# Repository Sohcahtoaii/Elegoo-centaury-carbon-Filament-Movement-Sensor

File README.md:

# Elegoo Centaury Carbon – Filament Movement Sensor  
### FR / EN – Capteur de mouvement de filament pour imprimante 3D

---

## 🇫🇷 Description (FR)

🔧 Ce projet est une **amélioration matérielle** pour l’imprimante **Elegoo Centaury Carbon**, permettant de détecter le mouvement du filament.  
Il est basé sur le travail de [Jonathan Rowny](https://github.com/jrowny/cc_sfs), avec comme principale contribution ici la **création d’un PCB personnalisé** pour faciliter l’intégration propre du capteur.

📦 **Capteur requis :**  
👉 Ce projet utilise le **BIGTREETECH Smart Filament Detector V2.0**, un capteur optique à encodeur rotatif.

🔌 **PCB personnalisé :**  
- Fichiers créés avec **KiCad**
- Connexion facile au capteur et à la Centaury
- Ports supplémentaires disponibles pour le **debug ou des améliorations futures**

📁 Tous les fichiers nécessaires sont disponibles dans le dossier `/pcb` :
- `.kicad_pcb`, `.sch`, fichiers Gerber, PDF
- Sérigraphie, dimensions, BOM (Bill of Materials)

---

## 🇬🇧 Description (EN)

🔧 This project is a **hardware upgrade** for the **Elegoo Centaury Carbon** 3D printer that adds **filament motion detection**.  
It is based on the work by [Jonathan Rowny](https://github.com/jrowny/cc_sfs), with the main contribution here being a **custom-designed PCB** to neatly integrate the sensor.

📦 **Required sensor:**  
👉 This project uses the **BIGTREETECH Smart Filament Detector V2.0**, an optical rotary encoder sensor.

🔌 **Custom PCB:**
- Designed with **KiCad**
- Easy connection to the sensor and the Centaury printer
- Additional ports are available for **debugging or future upgrades**

📁 All necessary files are in the `/pcb` folder:
- `.kicad_pcb`, `.sch`, Gerber files, PDFs
- Silkscreen, dimensions, BOM (Bill of Materials)

---

## 🔗 Projet original / Original Project

📚 Basé sur / Based on:  
👉 [Jonathan Rowny – cc_sfs](https://github.com/jrowny/cc_sfs)

---

## 🧰 Matériel requis / Required Hardware

- BIGTREETECH Smart Filament Detector V2.0  
- Résistances, connecteurs, composants SMD ou traversants  
- Câbles dupont ou connecteurs JST selon le montage  
- PCB personnalisé  
- Outils de soudure  
- Imprimante 3D : **Elegoo Centaury Carbon**

---

## ⚙️ Instructions de montage / Assembly Instructions

### 🇫🇷 En français

1. Soudez les composants sur le PCB selon le schéma si vous n'avez pas utilisé un service d’assemblage.  
2. Connectez le capteur BTT V2.0 au PCB.  
3. Branchez le PCB à l'imprimante selon le câblage prévu.  
4. Flashez le firmware proposé dans le projet de [Jonathan Rowny](https://github.com/jrowny/cc_sfs).  
5. Vérifiez la détection du filament via le firmware (compatible Marlin ou Klipper).  
6. Utilisez les **ports restants** pour du debug ou des extensions.

### 🇬🇧 In English

1. Solder the components onto the PCB, unless you're using an assembled PCB service.  
2. Connect the BTT Smart Filament Sensor V2.0 to the PCB.  
3. Connect the PCB to your Elegoo printer using the proper wiring.  
4. Flash the firmware provided in [Jonathan Rowny’s project](https://github.com/jrowny/cc_sfs).  
5. Verify filament movement detection through the firmware (Marlin or Klipper compatible).  
6. Use the **extra ports** for debugging or optional upgrades.

---
## 🔍 BOM interactif  
👉 [Voir le BOM interactif ici](https://sohcahtoaii.github.io/Elegoo-centaury-carbon-Filament-Movement-Sensor/)

## 🖼️ Images / Preview

---

## ❓ FAQ

**Q : Le capteur fonctionne-t-il avec d'autres imprimantes ?**  
A : Ce design est principalement prévu pour l’Elegoo Centaury Carbon, mais le PCB peut être adapté.

**Q : Peut-on ajouter d'autres fonctions ?**  
A : Oui, des **broches supplémentaires** sont disponibles pour extensions ou debug série.

**Q : Est-ce que je dois modifier le firmware ?**  
A : Non, le capteur est branché sur l’entrée de détection de fin de filament existante. Il fonctionne directement avec la pause automatique.

---

## 📜 Licence / License

**MIT License**  
Libre de modifier, réutiliser et redistribuer ce projet.

---

## 🙏 Remerciements / Credits

- 🔧 Idée originale et base logicielle : [Jonathan Rowny – cc_sfs](https://github.com/jrowny/cc_sfs)  
- 🧩 PCB personnalisé et adaptation Elegoo : *Sohcahtoaii*

---

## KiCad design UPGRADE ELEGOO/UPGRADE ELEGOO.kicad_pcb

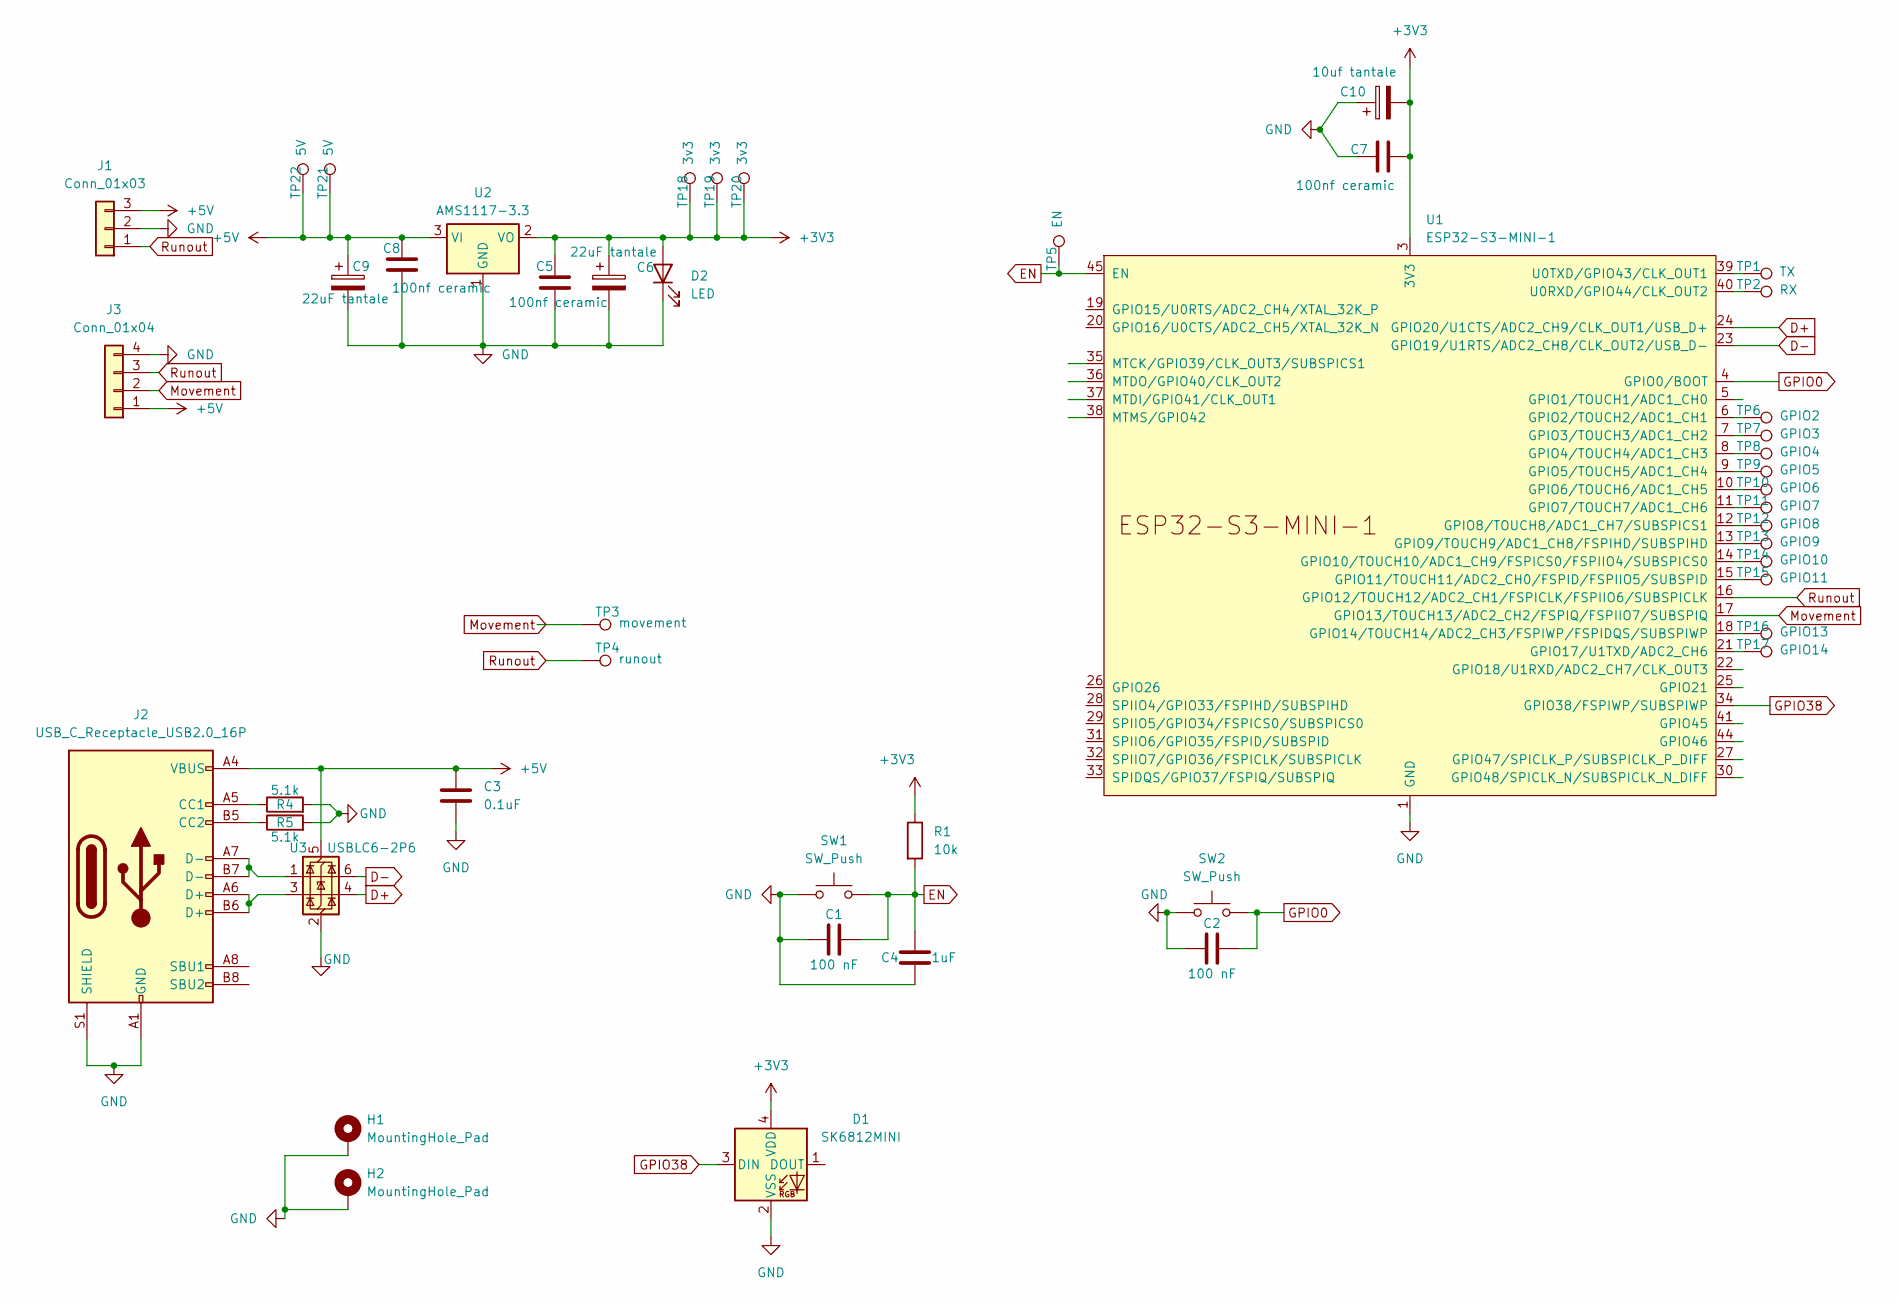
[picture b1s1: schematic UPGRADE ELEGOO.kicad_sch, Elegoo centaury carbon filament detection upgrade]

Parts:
C1, C2: 100 nF; C_0805_2012Metric_Pad1.18x1.45mm_HandSolder
C3: 0.1uF; C_0805_2012Metric_Pad1.18x1.45mm_HandSolder
C4: 1uF; C_0805_2012Metric_Pad1.18x1.45mm_HandSolder
C5, C7, C8: 100nf ceramic; C_0805_2012Metric_Pad1.18x1.45mm_HandSolder
C6: 22uF tantale; C_1206_3216Metric_Pad1.33x1.80mm_HandSolder
C9: 22uF tantale; C_1206_3216Metric
C10: 10uf tantale; C_1206_3216Metric_Pad1.33x1.80mm_HandSolder
D1: SK6812MINI; LED_SK6812MINI_PLCC4_3.5x3.5mm_P1.75mm
D2: LED; LED_0805_2012Metric
H1, H2: MountingHole_Pad; MountingHole_3.2mm_M3_ISO14580_Pad
J1: Conn_01x03; JST_PH_S3B-PH-K_1x03_P2.00mm_Horizontal
J2: USB_C_Receptacle_USB2.0_16P; USB_C_Receptacle_G-Switch_GT-USB-7010ASV
J3: Conn_01x04; JST_PH_S4B-PH-K_1x04_P2.00mm_Horizontal
R1: 10k; R_0805_2012Metric_Pad1.20x1.40mm_HandSolder
R4, R5: 5.1k; R_0805_2012Metric_Pad1.15x1.40mm
SW1, SW2: SW_Push; SW_Push_1P1T_NO_CK_KMR2
TP1: TX; TestPoint_THTPad_D2.0mm_Drill1.0mm
TP2: RX; TestPoint_THTPad_D2.0mm_Drill1.0mm
TP3: movement; TestPoint_THTPad_D2.0mm_Drill1.0mm
TP4: runout; TestPoint_THTPad_D2.0mm_Drill1.0mm
TP5: EN; TestPoint_THTPad_D2.0mm_Drill1.0mm
TP6: GPIO2; TestPoint_THTPad_D2.0mm_Drill1.0mm
TP7: GPIO3; TestPoint_THTPad_D2.0mm_Drill1.0mm
TP8: GPIO4; TestPoint_THTPad_D2.0mm_Drill1.0mm
TP9: GPIO5; TestPoint_THTPad_D2.0mm_Drill1.0mm
TP10: GPIO6; TestPoint_THTPad_D2.0mm_Drill1.0mm
TP11: GPIO7; TestPoint_THTPad_D2.0mm_Drill1.0mm
TP12: GPIO8; TestPoint_THTPad_D2.0mm_Drill1.0mm
TP13: GPIO9; TestPoint_THTPad_D2.0mm_Drill1.0mm
TP14: GPIO10; TestPoint_THTPad_D2.0mm_Drill1.0mm
TP15: GPIO11; TestPoint_THTPad_D2.0mm_Drill1.0mm
TP16: GPIO13; TestPoint_THTPad_D2.0mm_Drill1.0mm
TP17: GPIO14; TestPoint_THTPad_D2.0mm_Drill1.0mm
TP18, TP19, TP20: 3v3; TestPoint_THTPad_D2.0mm_Drill1.0mm
TP21, TP22: 5V; TestPoint_THTPad_D2.0mm_Drill1.0mm
U1: ESP32-S3-MINI-1
U2: AMS1117-3.3; SOT-223-3_TabPin2
U3: USBLC6-2P6; SOT-666

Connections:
+3V3: C5.1, C6.1, C7.2, C10.2, D1.4 (VDD), D2.2 (A), R1.1, TP18.1, TP19.1, TP20.1, U1.3 (3V3), U2.2 (VO)
+5V: C3.1, C8.1, C9.1, J1.3, J2.A4 (VBUS), J2.A9 (VBUS), J2.B4 (VBUS), J2.B9 (VBUS), J3.1, TP21.1, TP22.1, U2.3 (VI), U3.5 (VBUS)
D+: U1.24 (GPIO20/U1CTS/ADC2_CH9/CLK_OUT1/USB_D+), U3.4 (I/O2)
D-: U1.23 (GPIO19/U1RTS/ADC2_CH8/CLK_OUT2/USB_D-), U3.6 (I/O1)
EN: C1.2, C4.2, R1.2, SW1.2, TP5.1, U1.45 (EN)
GND: C1.1, C2.1, C3.2, C4.1, C5.2, C6.2, C7.1, C8.2, C9.2, C10.1, D1.2 (VSS), D2.1 (K), H1.1, H2.1, J1.2, J2.A1 (GND), J2.A12 (GND), J2.B1 (GND), J2.B12 (GND), J2.S1 (SHIELD), J3.4, R4.2, R5.2, SW1.1, SW2.1, U1.1 (GND), U1.2 (GND), U1.42 (GND), U1.43 (GND), U1.46 (GND), U1.47 (GND), U1.48 (GND), U1.49 (GND), U1.50 (GND), U1.51 (GND), U1.52 (GND), U1.53 (GND), U1.54 (GND), U1.55 (GND), U1.56 (GND), U1.57 (GND), U1.58 (GND), U1.59 (GND), U1.60 (GND), U1.61 (GND), U1.62 (GND), U1.63 (GND), U1.64 (GND), U1.65 (GND), U2.1 (GND), U3.2 (GND)
GPIO0: C2.2, SW2.2, U1.4 (GPIO0/BOOT)
GPIO38: D1.3 (DIN), U1.34 (GPIO38/FSPIWP/SUBSPIWP)
Movement: J3.2, TP3.1, U1.17 (GPIO13/TOUCH13/ADC2_CH2/FSPIQ/FSPIIO7/S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)
unnamed: J2.A5 (CC1), R4.1
unnamed: J2.B5 (CC2), R5.1
unnamed: J2.A6 (D+), J2.B6 (D+), U3.3 (I/O2)
unnamed: J2.A7 (D-), J2.B7 (D-), U3.1 (I/O1)
unnamed: TP6.1, U1.6 (GPIO2/TOUCH2/ADC1_CH1)
unnamed: TP7.1, U1.7 (GPIO3/TOUCH3/ADC1_CH2)
unnamed: TP8.1, U1.8 (GPIO4/TOUCH4/ADC1_CH3)
unnamed: TP9.1, U1.9 (GPIO5/TOUCH5/ADC1_CH4)
unnamed: TP10.1, U1.10 (GPIO6/TOUCH6/ADC1_CH5)
unnamed: TP11.1, U1.11 (GPIO7/TOUCH7/ADC1_CH6)
unnamed: TP12.1, U1.12 (GPIO8/TOUCH8/ADC1_CH7/SUBSPICS1)
unnamed: TP13.1, U1.13 (GPIO9/TOUCH9/ADC1_CH8/FSPIHD/SUBSPIHD)
unnamed: TP14.1, U1.14 (GPIO10/TOUCH10/ADC1_CH9/FSPICS0/FSPIIO4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)
unnamed: TP15.1, U1.15 (GPIO11/TOUCH11/ADC2_CH0/FSPID/FSPIIO5/S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)
unnamed: TP16.1, U1.18 (GPIO14/TOUCH14/ADC2_CH3/FSPIWP/FSPIDQS/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)
unnamed: TP17.1, U1.21 (GPIO17/U1TXD/ADC2_CH6)
unnamed: TP2.1, U1.40 (U0RXD/GPIO44/CLK_OUT2)
unnamed: TP1.1, U1.39 (U0TXD/GPIO43/CLK_OUT1)
Runout: J1.1, J3.3, TP4.1, U1.16 (GPIO12/TOUCH12/ADC2_CH1/FSPICLK/FSPIIO6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)

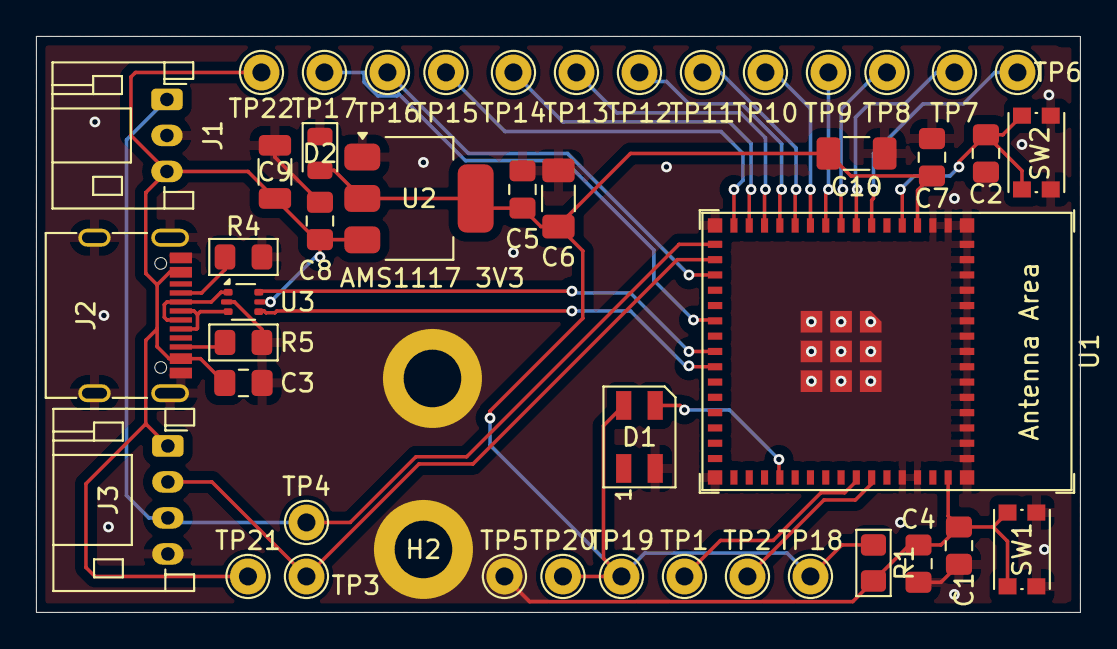
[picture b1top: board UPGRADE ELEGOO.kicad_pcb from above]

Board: 2 copper layers, 58.0 x 32.0 mm, 47 parts (0 on the bottom side), 28 nets.

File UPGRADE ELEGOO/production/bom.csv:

Designator,Footprint,Quantity,Value,LCSC Part #
"C1, C2",0805,2,100 nF,
C10,1206,1,10uf tantale,
C3,0805,1,0.1uF,
C4,0805,1,1uF,
"C5, C7, C8",0805,3,100nf ceramic,
"C6, C9",1206,2,22uF tantale,
D1,LED_SK6812MINI_PLCC4_3.5x3.5mm_P1.75mm,1,SK6812MINI,
D2,0805,1,LED,
J1,JST_PH_S3B-PH-K_1x03_P2.00mm_Horizontal,1,Conn_01x03,
J2,USB_C_Receptacle_G-Switch_GT-USB-7010ASV,1,USB_C_Receptacle_USB2.0_16P,
J3,JST_PH_S4B-PH-K_1x04_P2.00mm_Horizontal,1,Conn_01x04,
R1,0805,1,10k,
"R4, R5",0805,2,5.1k,
"SW1, SW2",SW_Push_1P1T_NO_CK_KMR2,2,SW_Push,
TP1,TestPoint_THTPad_D2.0mm_Drill1.0mm,1,TX,
TP10,TestPoint_THTPad_D2.0mm_Drill1.0mm,1,GPIO6,
TP11,TestPoint_THTPad_D2.0mm_Drill1.0mm,1,GPIO7,
TP12,TestPoint_THTPad_D2.0mm_Drill1.0mm,1,GPIO8,
TP13,TestPoint_THTPad_D2.0mm_Drill1.0mm,1,GPIO9,
TP14,TestPoint_THTPad_D2.0mm_Drill1.0mm,1,GPIO10,
TP15,TestPoint_THTPad_D2.0mm_Drill1.0mm,1,GPIO11,
TP16,TestPoint_THTPad_D2.0mm_Drill1.0mm,1,GPIO13,
TP17,TestPoint_THTPad_D2.0mm_Drill1.0mm,1,GPIO14,
"TP18, TP19, TP20",TestPoint_THTPad_D2.0mm_Drill1.0mm,3,3v3,
TP2,TestPoint_THTPad_D2.0mm_Drill1.0mm,1,RX,
"TP21, TP22",TestPoint_THTPad_D2.0mm_Drill1.0mm,2,5V,
TP3,TestPoint_THTPad_D2.0mm_Drill1.0mm,1,movement,
TP4,TestPoint_THTPad_D2.0mm_Drill1.0mm,1,runout,
TP5,TestPoint_THTPad_D2.0mm_Drill1.0mm,1,EN,
TP6,TestPoint_THTPad_D2.0mm_Drill1.0mm,1,GPIO2,
TP7,TestPoint_THTPad_D2.0mm_Drill1.0mm,1,GPIO3,
TP8,TestPoint_THTPad_D2.0mm_Drill1.0mm,1,GPIO4,
TP9,TestPoint_THTPad_D2.0mm_Drill1.0mm,1,GPIO5,
U1,ESP32-S3-MINI-1,1,ESP32-S3-MINI-1,
U2,SOT-223-3_TabPin2,1,AMS1117-3.3,
U3,SOT-666,1,USBLC6-2P6,

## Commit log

2025-07-25 Update README.md
    readme initial upload
2025-07-25 initial upload
2025-07-25 Rename Readme.md to index.html
